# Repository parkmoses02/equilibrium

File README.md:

# equilibrium
Double Inverted Pendulum Control - 6인 팀 프로젝트  이중 역진자 시스템의 동역학 모델링과 제어 알고리즘 구현을 위한 공동 개발 저장소입니다.

프로젝트 목표:
- 정확한 비선형/선형화 모델 개발
- 다양한 제어 기법(LQR, PID, MPC 등) 비교 및 적용
- 시뮬레이션 환경 구축 및 성능 분석
- 코드 품질과 문서화 유지

로컬 환경 구성 안내:
- [LOCAL_SETUP.md](LOCAL_SETUP.md)

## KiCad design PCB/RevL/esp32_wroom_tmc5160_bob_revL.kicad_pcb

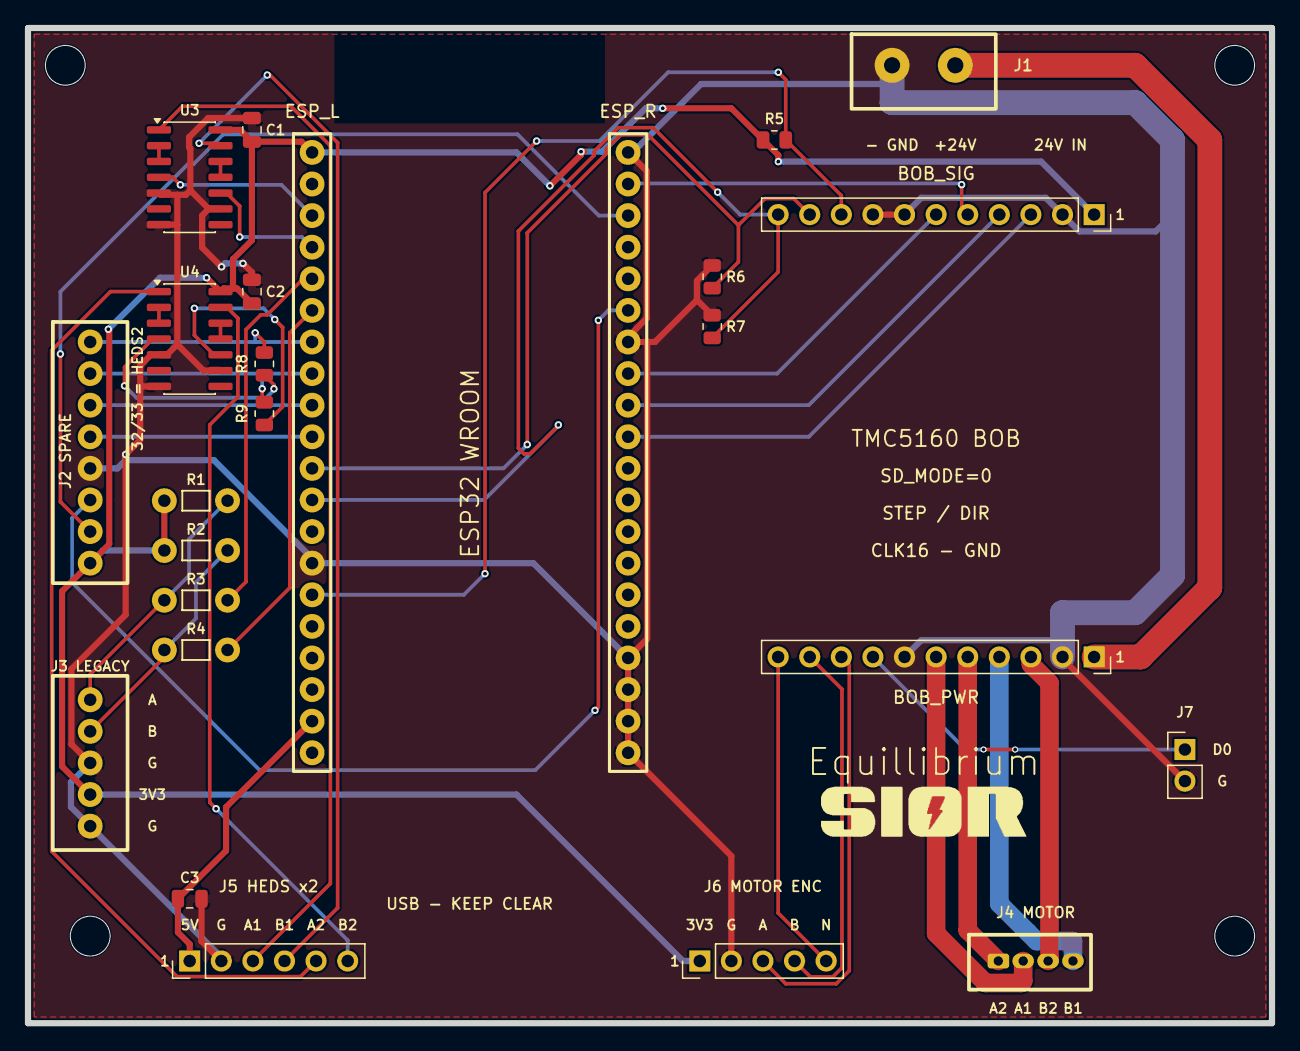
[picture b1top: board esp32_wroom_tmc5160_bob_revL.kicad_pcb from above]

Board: 2 copper layers, 100.0 x 80.0 mm, 29 parts (0 on the bottom side), 41 nets.

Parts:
BOB_PWR: 1x11 FEMALE 2.54mm; BOB_PWR
BOB_SIG: 1x11 FEMALE 2.54mm; BOB_SIG
C1: 100nF 16V X7R; C1
C2: 100nF 16V X7R; C2
C3: 10uF 10V X7R; C3
ESP_L: 1x20 2.54mm FEMALE SOCKET; ESP_L
ESP_R: 1x20 2.54mm FEMALE SOCKET; ESP_R
H1: M3_MOUNT; H1
H2: M3_MOUNT; H2
H3: M3_MOUNT; H3
H4: M3_MOUNT; H4
J1: 24V INPUT: 1=GND 2=+24V; J1
J2: SPARE GPIO / 1x8 2.54mm FEMALE SOCKET; J2
J3: LEGACY ENCODER 3V3; J3
J4: JST-PH B4B-PH-K 4-pin 2.00mm MALE; J4
J5: DUAL HEDS 5V; J5
J6: MOTOR ENCODER 3V3 ONLY; J6
J7: DIAG0 / GND; J7
R1: R_A_PULLUP_4K7; R1
R2: R_B_PULLUP_4K7; R2
R3: R_A_SERIES_100R; R3
R4: R_B_SERIES_100R; R4
R5: 10k EN default OFF; R5
R6: 100k STEP pull-down; R6
R7: 100k DIR pull-down; R7
R8: 100R; R8
R9: 100R; R9
U3: SN74LVC14AD; U3
U4: SN74LVC14AD; U4

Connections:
+3V3: BOB_SIG.1, C1.1, C2.1, ESP_L.L1, J2.8, J3.4, J6.1, R1.1, R2.1, R5.1, U3.14, U4.14
+5V: C3.1, ESP_L.L19, J5.1
ENC_A: ESP_L.L5, R3.2
ENC_A_RAW: J3.1, R1.2, R3.1
ENC_B: ESP_L.L6, R4.2
ENC_B_RAW: J3.2, R2.2, R4.1
GND: BOB_PWR.2, BOB_PWR.7, BOB_SIG.2, BOB_SIG.7, BOB_SIG.8, C1.2, C2.2, C3.2, ESP_L.L14, ESP_R.R1, ESP_R.R7, ESP_R.R17, ESP_R.R18, ESP_R.R19, ESP_R.R20, J1.1, J2.5, J3.3, J3.5, J5.2, J6.2, J7.2, R6.2, R7.2, U3.5, U3.7, U3.9, U4.5, U4.7, U4.9
HEDS1_A: ESP_L.L3, U3.4
HEDS1_A_5V: J5.3, U3.1
HEDS1_A_INV: U3.2, U3.3
HEDS1_B: ESP_L.L4, U3.10
HEDS1_B_5V: J5.4, U3.13
HEDS1_B_INV: U3.11, U3.12
HEDS2_A: R8.1, U4.4
HEDS2_A_5V: J5.5, U4.1
HEDS2_A_INV: U4.2, U4.3
HEDS2_B: R9.1, U4.10
HEDS2_B_5V: J5.6, U4.13
HEDS2_B_INV: U4.11, U4.12
IO21: ESP_R.R6, J2.6
IO22: ESP_R.R3, J2.7
IO25: ESP_L.L9, J2.3
IO26: ESP_L.L10, J2.4
IO32: ESP_L.L7, J2.1, R8.2
IO33: ESP_L.L8, J2.2, R9.2
M_A1: BOB_PWR.6, J4.2
M_A2: BOB_PWR.5, J4.1
M_B1: BOB_PWR.4, J4.4
M_B2: BOB_PWR.3, J4.3
M_ENCA: BOB_PWR.9, J6.3
M_ENCB: BOB_PWR.10, J6.4
M_ENCN: BOB_PWR.11, J6.5
SPI_CS: BOB_SIG.3, ESP_R.R10
SPI_MISO: BOB_SIG.6, ESP_R.R8
SPI_MOSI: BOB_SIG.5, ESP_R.R2
SPI_SCK: BOB_SIG.4, ESP_R.R9
TMC_DIAG0: BOB_PWR.8, J7.1
TMC_DIR: BOB_SIG.11, ESP_L.L12, R7.1
TMC_EN: BOB_SIG.9, ESP_L.L15, R5.2
TMC_STEP: BOB_SIG.10, ESP_L.L11, R6.1
VMOT: BOB_PWR.1, J1.2

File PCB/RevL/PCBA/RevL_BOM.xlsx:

Comment | Designator | Footprint | LCSC Part #
Female socket 1x20 2.54mm vertical | ESP_L,ESP_R | PinSocket_1x20_P2.54mm_Vertical | C7509519
Female socket 1x11 2.54mm vertical | BOB_SIG,BOB_PWR | PinSocket_1x11_P2.54mm_Vertical
WJ500V-5.08-2P screw terminal | J1 | TerminalBlock_1x02_P5.08mm | C8465
Female socket 1x8 2.54mm vertical | J2 | PinSocket_1x08_P2.54mm_Vertical | C27438
Female socket 1x5 2.54mm vertical | J3 | PinSocket_1x05_P2.54mm_Vertical | C7509517
B4B-PH-K-S(LF)(SN) JST PH 4pin 2mm | J4 | JST_PH_B4B-PH-K_1x04_P2.00mm_Vertical | C131334
Male pin header 1x6 2.54mm vertical | J5 | PinHeader_1x06_P2.54mm_Vertical
Male pin header 1x5 2.54mm vertical | J6 | PinHeader_1x05_P2.54mm_Vertical
Male pin header 1x2 2.54mm vertical | J7 | PinHeader_1x02_P2.54mm_Vertical
SN74LVC14ADR | U3,U4 | SOIC-14_3.9x8.7mm_P1.27mm | C133541
100nF 16V X7R 10% | C1,C2 | C_0805_2012Metric
10uF 10V X7R 20% | C3 | C_0805_2012Metric
10k 1% 0.125W | R5 | R_0805_2012Metric
100k 1% 0.125W | R6,R7 | R_0805_2012Metric
100R 1% 0.125W | R8,R9 | R_0805_2012Metric

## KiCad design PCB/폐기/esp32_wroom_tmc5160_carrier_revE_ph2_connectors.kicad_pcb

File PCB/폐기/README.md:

# Freenove ESP32 WROOM + TMC5160T Pro Carrier Rev.C Routed

Two-layer routed carrier reconstructed from the supplied images.

## Mechanical assumptions

- PCB: 100 x 80 mm, four M3 holes
- ESP32 WROOM headers: 2.54 mm pitch, 20 pins per side, assumed 27.94 mm row spacing
- TMC5160T Pro: 2.54 mm pitch, assumed 15.24 mm row spacing

## Routing rules applied

- VMOT: 2.00 mm
- Motor phases A1/A2/B1/B2: 1.50 mm
- +5V: 1.00 mm
- +3V3: 0.50 mm
- Digital and encoder signals: 0.30 mm
- Ground zones: F.Cu and B.Cu
- Encoder: 4.7k pull-ups to 3.3 V and 100-ohm series resistors

## Before fabrication

GPIO16 and GPIO17 are left unconnected. Press B in KiCad to refill zones and run DRC. Confirm both module footprints and every connector orientation with a 1:1 paper print and the real hardware before ordering.

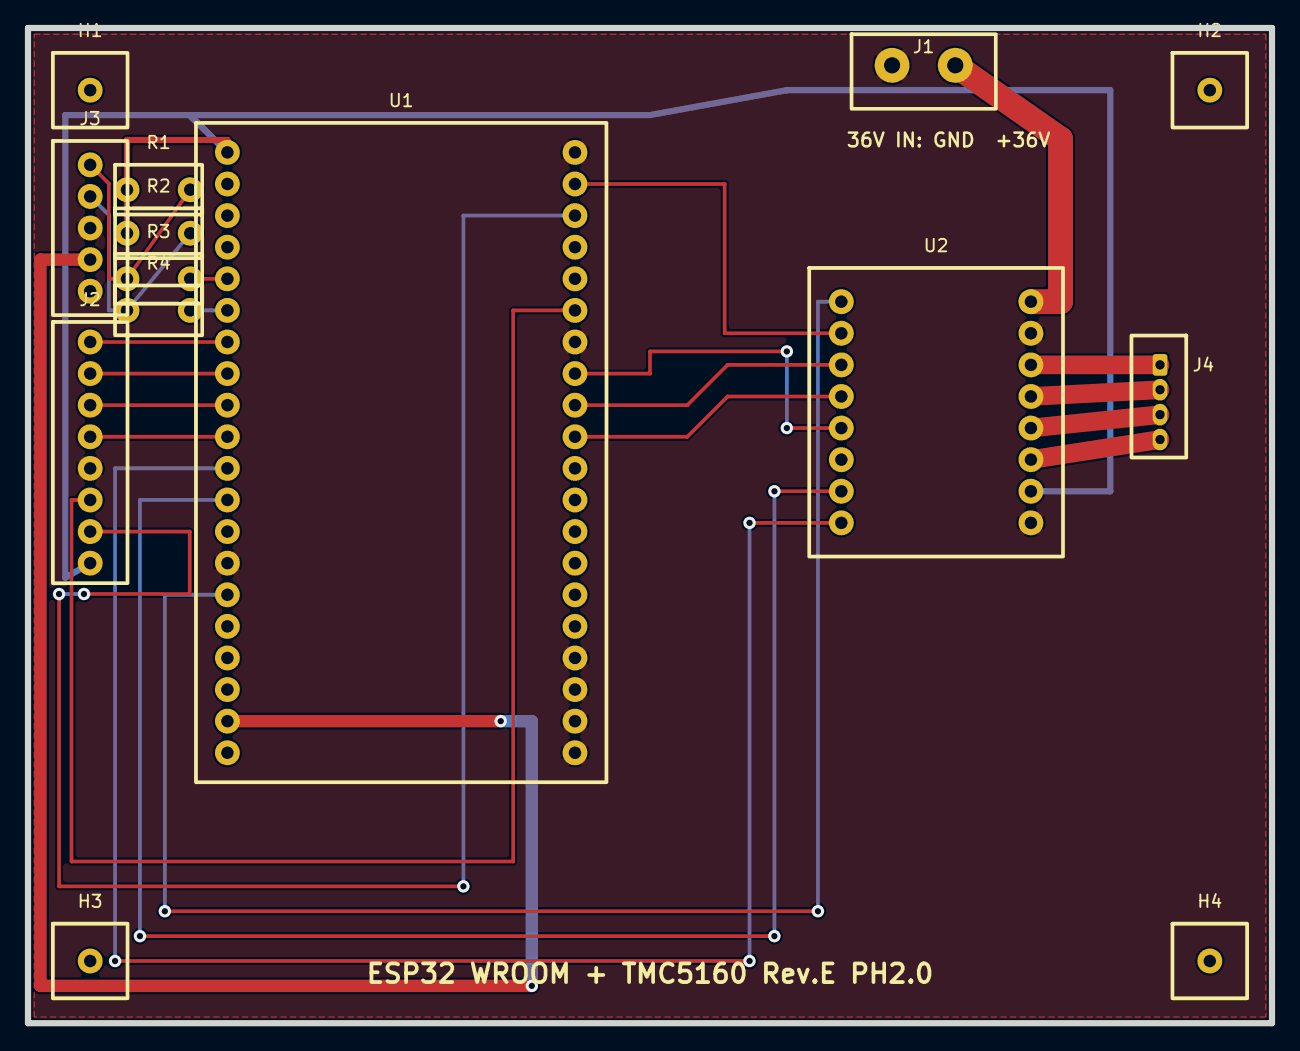
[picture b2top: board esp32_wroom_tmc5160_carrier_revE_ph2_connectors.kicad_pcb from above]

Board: 2 copper layers, 100.0 x 80.0 mm, 14 parts (0 on the bottom side), 25 nets.

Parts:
H1, H2, H3, H4: M3_MOUNT
J1: 36V INPUT 2P 5.08mm TERMINAL; TERMINAL_BLOCK_2P_5.08
J2: SPARE GPIO / 1x8 2.54mm FEMALE SOCKET; IO_1x8_2.54_VERTICAL
J3: ENCODER / 1x5 2.54mm FEMALE SOCKET; ENCODER_1x5_2.54_VERTICAL
J4: JST-PH B4B-PH-K 4-pin 2.00mm MALE; JST_PH_B4B-PH-K_1x04_P2.00mm_Vertical
R1: R_A_PULLUP_4K7
R2: R_B_PULLUP_4K7
R3: R_A_SERIES_100R
R4: R_B_SERIES_100R
U1: FREENOVE ESP32 WROOM / 1x20 2.54mm FEMALE SOCKET 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; FREENOVE_ESP32_WROOM_2x20
U2: TMC5160T PRO / 1x8 2.54mm FEMALE SOCKET x2; TMC5160T_PRO_2x8

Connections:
+3V3: J2.8, R1.1, R2.1, U1.L1, U2.15
+5V: J3.4, U1.L19
ENC_A: R3.2, U1.L5
ENC_A_RAW: J3.1, R1.2, R3.1
ENC_B: R4.2, U1.L6
ENC_B_RAW: J3.2, R2.2, R4.1
GND: J1.1, J2.5, J3.3, J3.5, U1.L14, U1.R1, U1.R7, U1.R17, U1.R18, U1.R19, U1.R20, U2.10, U2.16
IO21: J2.6, U1.R6
IO22: J2.7, U1.R3
IO25: J2.3, U1.L9
IO26: J2.4, U1.L10
IO32: J2.1, U1.L7
IO33: J2.2, U1.L8
M_A1: J4.2, U2.12
M_A2: J4.1, U2.11
M_B1: J4.4, U2.14
M_B2: J4.3, U2.13
SPI_CS: U1.R10, U2.4
SPI_MISO: U1.R8, U2.5
SPI_MOSI: U1.R2, U2.2
SPI_SCK: U1.R9, U2.3
TMC_DIR: U1.L11, U2.8
TMC_EN: U1.L15, U2.1
TMC_STEP: U1.L12, U2.7
VMOT: J1.2, U2.9

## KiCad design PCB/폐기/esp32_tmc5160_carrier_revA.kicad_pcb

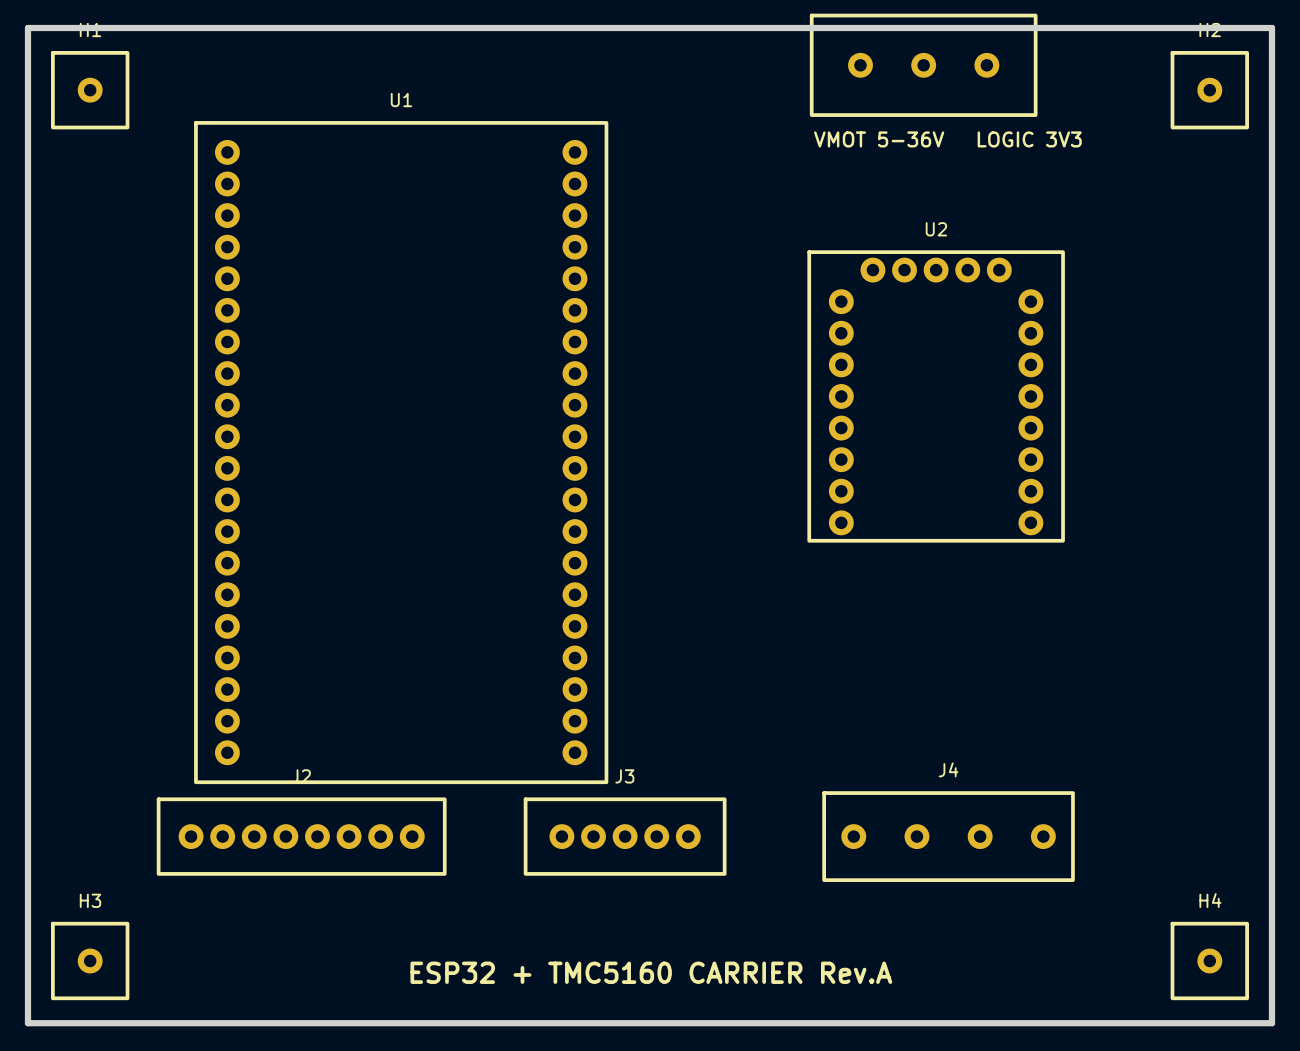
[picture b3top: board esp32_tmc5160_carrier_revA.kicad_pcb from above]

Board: 2 copper layers, 100.0 x 80.0 mm, 10 parts (0 on the bottom side), 24 nets, no tracks yet.

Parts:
H1, H2, H3, H4: M3_MOUNT
J1: POWER_VMOT_3P_5.08
J2: IO_1x8_2.54
J3: ENCODER_1x5_2.54
J4: MOTOR_1x4_5.08
U1: FREENOVE_ESP32_WROVER_CAM_2x20
U2: TMC5160T_PRO_2x8

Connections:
+3V3: J2.8, U1.L1, U2.15
+5V: J1.2, J3.4, U1.L19
ENC_A: J3.2, U2.20
ENC_B: J3.1, U2.19
ENC_N: J3.5, U2.21
GND: J1.1, J2.1, J3.3, U1.L14, U1.R1, U1.R7, U1.R11, U1.R12, U1.R20, U2.10, U2.16
IO21: J2.2, U1.R6
IO22: J2.3, U1.R3
IO25: J2.4, U1.L9
IO26: J2.5, U1.L10
IO32: J2.6, U1.L7
IO33: J2.7, U1.L8
M_A1: J4.1, U2.12
M_A2: J4.2, U2.11
M_B1: J4.3, U2.14
M_B2: J4.4, U2.13
SPI_CS: U1.R10, U2.4
SPI_MISO: U1.R8, U2.5
SPI_MOSI: U1.R2, U2.2
SPI_SCK: U1.R9, U2.3
TMC_DIR: U1.L11, U2.8
TMC_EN: U1.L15, U2.1
TMC_STEP: U1.L12, U2.7
VMOT: J1.3, U2.9

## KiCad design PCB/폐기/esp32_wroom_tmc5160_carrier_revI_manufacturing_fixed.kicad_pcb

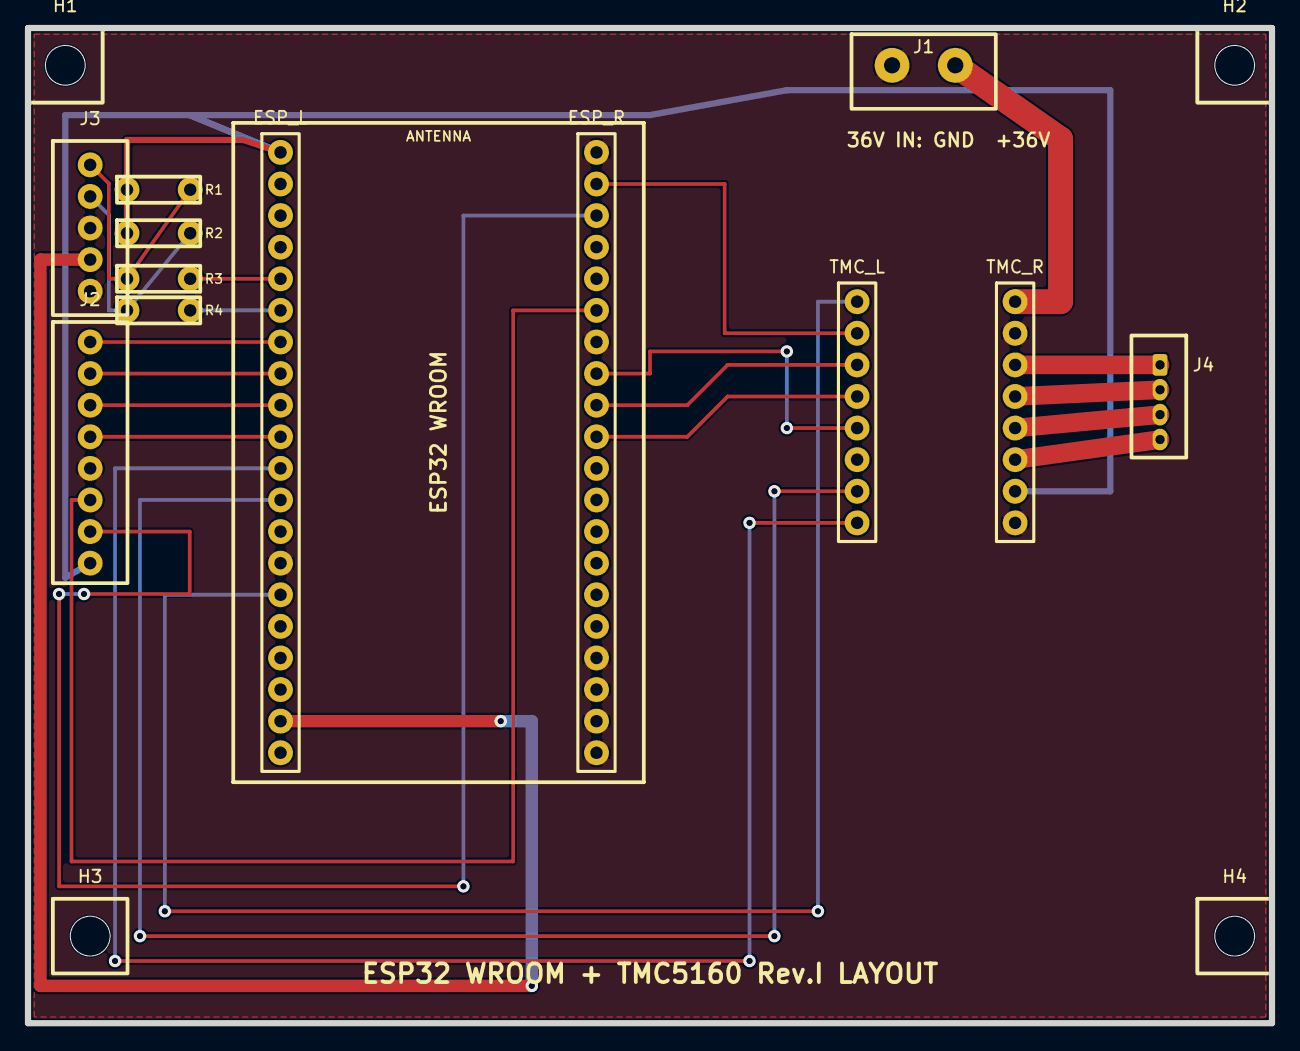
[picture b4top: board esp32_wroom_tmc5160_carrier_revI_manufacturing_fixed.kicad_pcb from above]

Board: 2 copper layers, 100.0 x 80.0 mm, 16 parts (0 on the bottom side), 25 nets.

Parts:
ESP_L: 1x20 2.54mm FEMALE SOCKET; ESP_L_1x20_PCBA
ESP_R: 1x20 2.54mm FEMALE SOCKET; ESP_R_1x20_PCBA
H1, H2, H3, H4: M3_MOUNT
J1: 36V INPUT 2P 5.08mm TERMINAL; TERMINAL_BLOCK_2P_5.08
J2: SPARE GPIO / 1x8 2.54mm FEMALE SOCKET; IO_1x8_2.54_VERTICAL
J3: ENCODER / 1x5 2.54mm FEMALE SOCKET; ENCODER_1x5_2.54_VERTICAL
J4: JST-PH B4B-PH-K 4-pin 2.00mm MALE; JST_PH_B4B-PH-K_1x04_P2.00mm_Vertical
R1: R_A_PULLUP_4K7
R2: R_B_PULLUP_4K7
R3: R_A_SERIES_100R
R4: R_B_SERIES_100R
TMC_L: 1x8 2.54mm FEMALE SOCKET; TMC_L_1x08_PCBA
TMC_R: 1x8 2.54mm FEMALE SOCKET; TMC_R_1x08_PCBA

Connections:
+3V3: ESP_L.L1, J2.8, R1.1, R2.1, TMC_R.15
+5V: ESP_L.L19, J3.4
ENC_A: ESP_L.L5, R3.2
ENC_A_RAW: J3.1, R1.2, R3.1
ENC_B: ESP_L.L6, R4.2
ENC_B_RAW: J3.2, R2.2, R4.1
GND: ESP_L.L14, ESP_R.R1, ESP_R.R7, ESP_R.R17, ESP_R.R18, ESP_R.R19, ESP_R.R20, J1.1, J2.5, J3.3, J3.5, TMC_R.10, TMC_R.16
IO21: ESP_R.R6, J2.6
IO22: ESP_R.R3, J2.7
IO25: ESP_L.L9, J2.3
IO26: ESP_L.L10, J2.4
IO32: ESP_L.L7, J2.1
IO33: ESP_L.L8, J2.2
M_A1: J4.2, TMC_R.12
M_A2: J4.1, TMC_R.11
M_B1: J4.4, TMC_R.14
M_B2: J4.3, TMC_R.13
SPI_CS: ESP_R.R10, TMC_L.4
SPI_MISO: ESP_R.R8, TMC_L.5
SPI_MOSI: ESP_R.R2, TMC_L.2
SPI_SCK: ESP_R.R9, TMC_L.3
TMC_DIR: ESP_L.L11, TMC_L.8
TMC_EN: ESP_L.L15, TMC_L.1
TMC_STEP: ESP_L.L12, TMC_L.7
VMOT: J1.2, TMC_R.9

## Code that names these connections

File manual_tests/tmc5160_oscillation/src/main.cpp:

#include <Arduino.h>
#include <SPI.h>

// ESP32 WROOM + carrier Rev.J pin map.
constexpr uint8_t PIN_TMC_EN   = 13;  // Active LOW
constexpr uint8_t PIN_TMC_STEP = 14;
constexpr uint8_t PIN_TMC_DIR  = 27;
constexpr uint8_t PIN_TMC_CS   = 5;
constexpr uint8_t PIN_SPI_MISO = 19;
constexpr uint8_t PIN_SPI_MOSI = 23;
constexpr uint8_t PIN_SPI_SCK  = 18;

// Conservative first-test motion: 200 microsteps/s for one second.
constexpr uint32_t MOVE_TIME_MS = 1000;
constexpr uint32_t PAUSE_TIME_MS = 1000;
constexpr uint32_t STEP_HALF_PERIOD_US = 2500;

constexpr uint8_t REG_GCONF        = 0x00;
constexpr uint8_t REG_IOIN         = 0x04;
constexpr uint8_t REG_GLOBALSCALER = 0x0B;
constexpr uint8_t REG_IHOLD_IRUN   = 0x10;
constexpr uint8_t REG_TPOWERDOWN   = 0x11;
constexpr uint8_t REG_CHOPCONF     = 0x6C;
constexpr uint8_t WRITE_FLAG       = 0x80;

SPISettings tmcSpi(1000000, MSBFIRST, SPI_MODE3);

void writeRegister(uint8_t address, uint32_t value) {
  SPI.beginTransaction(tmcSpi);
  digitalWrite(PIN_TMC_CS, LOW);
  SPI.transfer(address | WRITE_FLAG);
  SPI.transfer(static_cast<uint8_t>(value >> 24));
  SPI.transfer(static_cast<uint8_t>(value >> 16));
  SPI.transfer(static_cast<uint8_t>(value >> 8));
  SPI.transfer(static_cast<uint8_t>(value));
  digitalWrite(PIN_TMC_CS, HIGH);
  SPI.endTransaction();
}

uint32_t readRegister(uint8_t address) {
  // TMC5160 returns the requested register on the following SPI transaction.
  for (uint8_t transaction = 0; transaction < 2; ++transaction) {
    SPI.beginTransaction(tmcSpi);
    digitalWrite(PIN_TMC_CS, LOW);
    SPI.transfer(address & 0x7F);
    SPI.transfer(0);
    SPI.transfer(0);
    SPI.transfer(0);
    SPI.transfer(0);
    digitalWrite(PIN_TMC_CS, HIGH);
    SPI.endTransaction();
  }

  SPI.beginTransaction(tmcSpi);
  digitalWrite(PIN_TMC_CS, LOW);
  SPI.transfer(address & 0x7F);
  uint32_t value = static_cast<uint32_t>(SPI.transfer(0)) << 24;
  value |= static_cast<uint32_t>(SPI.transfer(0)) << 16;
  value |= static_cast<uint32_t>(SPI.transfer(0)) << 8;
  value |= static_cast<uint32_t>(SPI.transfer(0));
  digitalWrite(PIN_TMC_CS, HIGH);
  SPI.endTransaction();
  return value;
}

[[noreturn]] void stopWithError(const char *message) {
  digitalWrite(PIN_TMC_EN, HIGH);
  Serial.println(message);
  Serial.println("Driver remains DISABLED. Remove VM power before checking wiring.");
  while (true) delay(1000);
}

void configureDriver() {
  // SpreadCycle, normal STEP/DIR operation.
  writeRegister(REG_GCONF, 0x00000000);

  // BTT TMC5160 V1.0 has 0.075 ohm sense resistors.
  // IHOLD=4, IRUN=8, IHOLDDELAY=6 and GLOBALSCALER=128 provide a
  // deliberately conservative first-test current (roughly 0.3-0.4 A RMS).
  writeRegister(REG_GLOBALSCALER, 128);
  writeRegister(REG_IHOLD_IRUN, (6UL << 16) | (8UL << 8) | 4UL);
  writeRegister(REG_TPOWERDOWN, 10);

  // 16 microsteps, TOFF=3, HSTRT=4, HEND=1, TBL=2.
  const uint32_t chopconf = (4UL << 24) | (2UL << 15) |
                            (1UL << 7) | (4UL << 4) | 3UL;
  writeRegister(REG_CHOPCONF, chopconf);
}

void moveForOneSecond(bool direction) {
  digitalWrite(PIN_TMC_DIR, direction ? HIGH : LOW);
  delayMicroseconds(20);

  const uint32_t deadline = millis() + MOVE_TIME_MS;
  while (static_cast<int32_t>(deadline - millis()) > 0) {
    digitalWrite(PIN_TMC_STEP, HIGH);
    delayMicroseconds(STEP_HALF_PERIOD_US);
    digitalWrite(PIN_TMC_STEP, LOW);
    delayMicroseconds(STEP_HALF_PERIOD_US);
  }
}

void setup() {
  pinMode(PIN_TMC_EN, OUTPUT);
  pinMode(PIN_TMC_STEP, OUTPUT);
  pinMode(PIN_TMC_DIR, OUTPUT);
  pinMode(PIN_TMC_CS, OUTPUT);

  // Keep the power stage disabled until communication and configuration pass.
  digitalWrite(PIN_TMC_EN, HIGH);
  digitalWrite(PIN_TMC_STEP, LOW);
  digitalWrite(PIN_TMC_DIR, LOW);
  digitalWrite(PIN_TMC_CS, HIGH);

  Serial.begin(115200);
  SPI.begin(PIN_SPI_SCK, PIN_SPI_MISO, PIN_SPI_MOSI, PIN_TMC_CS);

  Serial.println();
  Serial.println("TMC5160 cautious oscillation test");
  Serial.println("Motor must be unloaded; use 12 V VM and a heatsink.");
  Serial.println("Starting in 3 seconds...");
  delay(3000);

  const uint32_t ioin = readRegister(REG_IOIN);
  const uint8_t version = static_cast<uint8_t>(ioin >> 24);
  Serial.printf("IOIN=0x%08lX, VERSION=0x%02X\n", ioin, version);
  if (version != 0x30) {
    stopWithError("ERROR: TMC5160 SPI response is invalid.");
  }

  configureDriver();
  digitalWrite(PIN_TMC_EN, LOW);
  Serial.println("Driver enabled. Beginning 1 s left/right motion.");
}

void loop() {
  Serial.println("Direction A: 1 second");
  moveForOneSecond(false);
  delay(PAUSE_TIME_MS);

  Serial.println("Direction B: 1 second");
  moveForOneSecond(true);
  delay(PAUSE_TIME_MS);
}

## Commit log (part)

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2026-03-26 Format README for better readability
2026-04-03 아무거나
2026-04-03 test commit
2026-04-03 ㅇㄹㅇㄹㅇ
2026-04-03 test
2026-04-03 bin file and calculation code
2026-04-03 food
2026-04-03 test2
2026-04-03 setup
2026-04-03 템플릿 수정
2026-04-03 uv 사용법
2026-04-03 파일 정리
2026-04-04 vs code commit 설정
2026-04-24 시뮬레이션 프로그램 수정
2026-05-01 단진자 시뮬레이션 추가
2026-05-01 단일진자 업그레이드
2026-05-21 chore: remove orphaned pip package files and caches from virtual environment
2026-05-21 chore: initialize project with Python 3.13 and uv dependency management
2026-05-21 docs: update local setup guide to use uv for environment and dependency management
2026-05-21 chore: remove .vscode from version control
2026-05-21 separate LQR
2026-05-24 Replace magdi branch with current Balance_ESP32C3_1_1 workspace
2026-05-24 일단 업데이트
2026-05-25 시뮬구체화
